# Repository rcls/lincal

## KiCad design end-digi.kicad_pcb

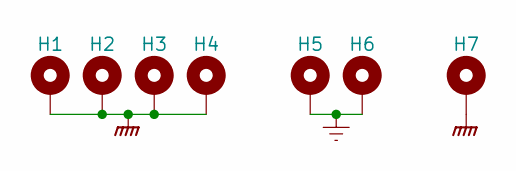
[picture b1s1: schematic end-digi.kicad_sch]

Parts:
H1, H2, H3, H4: MountingHole_Pad; MountingHole_3.2mm_M3_DIN965_Pad
H5, H6, H7: MountingHole_Pad; MountingHole_6.8mm

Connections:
Earth: H5.1, H6.1
GNDPWR: H1.1, H2.1, H3.1, H4.1, H7.1

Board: 2 copper layers, 7 parts (0 on the bottom side), 2 nets, no tracks yet.

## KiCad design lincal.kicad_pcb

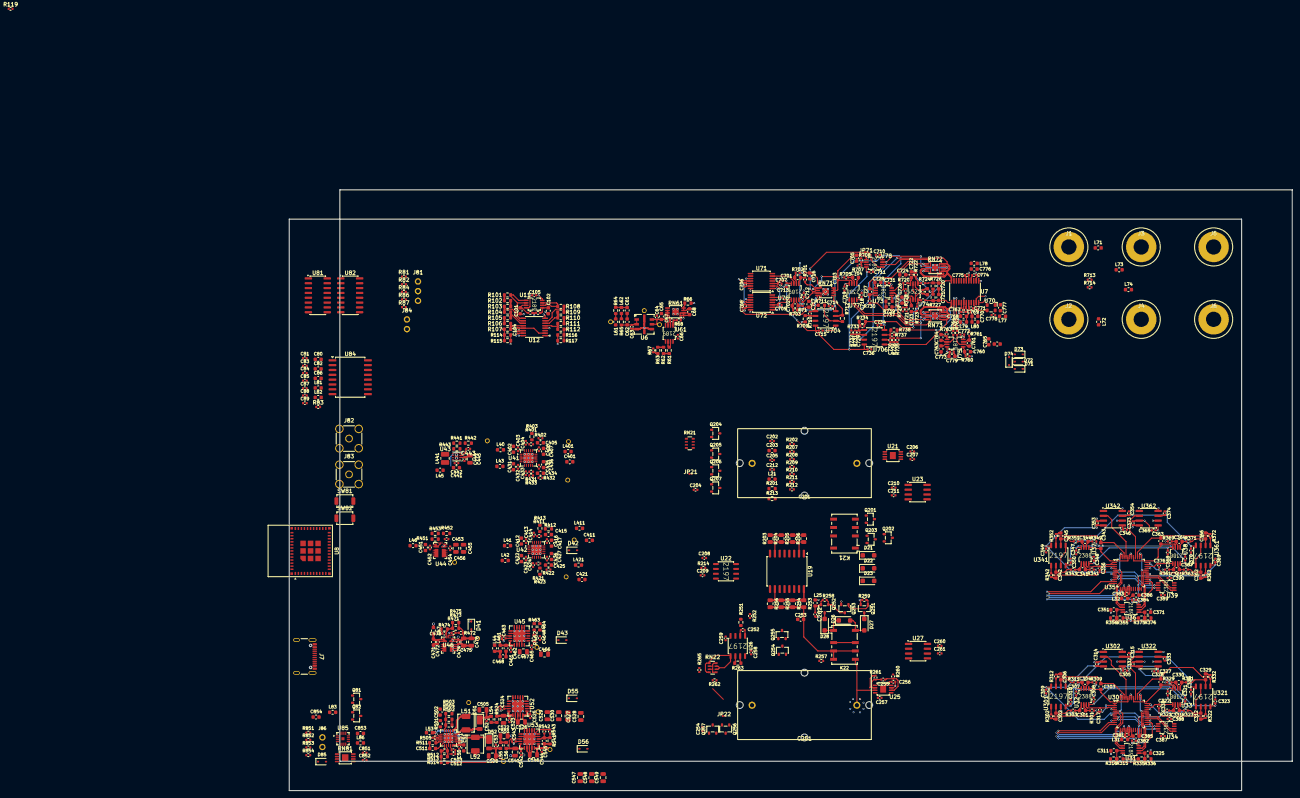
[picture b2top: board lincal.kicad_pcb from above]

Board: 4 copper layers, 263.3 x 157.7 mm, 594 parts (0 on the bottom side), 325 nets.

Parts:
C50, C52, C53, C66, C85, C87, C88, C89, C105, C206, C207, C208, C209, C210, C211, C256, C257, C258, C259, C260, C261, C309, C310, C314, C315, C323, C324, C332, C333, C349, C350, C353, C354, C369, C370, C373, C374, C382, C384, C523, C525, C542, C544, C706, C707, C708, C709, C710, C711, C712, C713, C714, C715, C734, C736, C772, C773: 0u1; C_0402_1005Metric
C51, C61, C62, C65, C80, C82, C86, C385, C386, C401, C402, C407, C411, C412, C417, C421, C422, C427, C431, C436, C441, C451, C461, C468, C471, C725, C733, C768, C770, C776, C777, C779, C853, C854: 10u; C_0603_1608Metric
C63, C64, C81, C83, C84, C104, C212, C262, C305, C307, C308, C321, C322, C327, C346, C347, C348, C365, C367, C368, C381, C383, C387, C388, C389, C390, C403, C404, C406, C413, C414, C416, C423, C424, C426, C432, C433, C435, C442, C444, C452, C454, C462, C463, C465, C472, C474, C503, C512, C524, C543, C718, C719, C731, C732, C767, C769, C771, C774, C775, C778, C851, C852: 1u; C_0402_1005Metric
C67, C202, C204, C205, C252, C254, C255, C317, C335, C356, C376, C703: 0n1; C_0402_1005Metric
C68, C101, C102, C203, C253, C311, C325, C351, C371, C405, C415, C425, C434, C464, C545, C716, C717, C720, C721, C727, C728, C760, C762, C763, C765: 10n; C_0603_1608Metric
C201, C251: 10u; C_Rect_L31.5mm_W15.0mm_P27.50mm_MKS4
C301, C302, C303, C304, C306, C312, C328, C329, C330, C331, C341, C342, C343, C344, C345, C361, C362, C363, C364, C366, C511, C701, C702, C704, C705, C722, C723, C724, C761, C764: 330p; C_0603_1608Metric
C443: 220p; C_0402_1005Metric
C445, C455, C456, C466, C467, C475, C476: 22u; C_0805_2012Metric
C453, C473: 22p; C_0402_1005Metric
C502: 1n; C_0603_1608Metric
C505, C508, C522, C526, C527, C528, C529, C530, C541, C546, C547, C548, C549, C551: 10u; C_0805_2012Metric
C726: 470n; C_0402_1005Metric
C729, C730: 10p; C_0402_1005Metric
C737: 10p; C_0603_1608Metric
D21, D22, D23, D26, D27, D28: SM4007PL; D_SOD-123FL
D41, D42, D43, D55, D56, D71, D72, D73, D74: 1N5819WS; D_SOD-323
D51, D52: DFLS140; D_PowerDI-123
D85: BZX384 5V6; D_SOD-323
J1, J2, J3, J4, J5, J6: Conn_01x01_Socket; Plated_Hole_D4.0mm_10mm
J7: USB_C_Receptacle_USB2.0_16P; USB_C_Receptacle_GCT_USB4105-xx-A_16P_TopMnt_Horizontal
J81: Conn_01x03_Pin; PinHeader_1x03_P2.54mm_Vertical
J82, J83: Conn_Coaxial; SMA_Amphenol_901-144_Vertical
J84, J86: Conn_01x02_Pin; PinHeader_1x02_P2.54mm_Vertical
JP21, JP22: SolderJumper_2_Open; JumperOpen
JP71: SolderJumper_2_Bridged; JumperClosed
K21, K22: G6K-2FY, 5V; Relay_DPDT_Omron_G6K-2G-Y
L21, L25, L31, L32, L40, L41, L42, L43, L44, L45, L47, L54, L55, L56, L61, L62, L77, L78, L79, L80, L82, L83, L401, L411, L421, L461: 600; L_0603_1608Metric
L46, L53, L71, L72, L73, L74, L81, L86: 100; L_0603_1608Metric
L51, L52: 10u; L_TechFuse_SL0420
L441: 1u5; L_1008_2520Metric
NT61: NetTie_2; NetTie-2_SMD_Pad0.5mm
Q81: Si2301CDS; SOT-23
Q82, Q201, Q203, Q204, Q205, Q206, Q207, Q251, Q253, Q254, Q255, Q256, Q257: AO3400A; SOT-23
Q202, Q252: AO3401A; SOT-23
R61, R62, R726, R727: 10k; R_0603_1608Metric
R63, R524: 1; R_0603_1608Metric
R64, R65: 2R2; R_0603_1608Metric
R66: 4k99; R_0603_1608Metric
R67, R81, R86, R87, R207, R208, R257, R258, R401, R411, R421, R431, R472, R542, R728, R729, R731, R736: 10k; R_0402_1005Metric
R68, R71, R210, R260, R701, R714, R724, R725, R761, R763: 10; R_0402_1005Metric
R82, R212, R262, R720, R721, R722, R723: 1k; R_0402_1005Metric
R83: 33; R_0402_1005Metric
R84, R113, R118, R119, R713, R730, R760: 100; R_0402_1005Metric
R101, R102, R103, R104, R109: 604; R_0603_1608Metric
R105, R106, R107, R110, R111, R112, R315, R316, R335, R336, R355, R356, R375, R376: 100; R_0603_1608Metric
R108: 47k5; R_0603_1608Metric
R114: 1k37; R_0603_1608Metric
R115: 150k; R_0603_1608Metric
R116: 24k9; R_0603_1608Metric
R117: 1M5; R_0603_1608Metric
R201, R251, R709: 16k; R_0603_1608Metric
R202, R209, R252, R259, R543, R710, R732, R735, R853, R854: 100k; R_0402_1005Metric
R203, R204, R205, R206, R253, R254, R255, R256: 1k; R_0805_2012Metric
R211, R261, R301, R302, R303, R309, R311, R312, R321, R322, R323, R329, R331, R332, R341, R342, R343, R349, R351, R352, R361, R362, R363, R369, R371, R372, R702, R703, R705, R707, R708, R762, R764: 330; R_0402_1005Metric
R213, R263: 8k2; R_0603_1608Metric
R214, R265: 200; R_0402_1005Metric
R402, R432, R505: 51k; R_0402_1005Metric
R403: 180k; R_0603_1608Metric
R412, R451, R473: 30k; R_0603_1608Metric
R413: 240k; R_0603_1608Metric
R422, R462: 20k; R_0402_1005Metric
R423: 160k; R_0603_1608Metric
R433: 56k; R_0402_1005Metric
R441: 2M; R_0603_1608Metric
R442: 360k; R_0603_1608Metric
R443: 91k; R_0603_1608Metric
R452, R474, R541: 130k; R_0603_1608Metric
R453, R475: 750k; R_0603_1608Metric
R463: 24k; R_0603_1608Metric
R464: 68k; R_0603_1608Metric
R471: 22k; R_0402_1005Metric
R501, R711, R712: 33k; R_0603_1608Metric
R502: 43k; R_0603_1608Metric
R503, R514: 1M; R_0603_1608Metric
R504: 1M3; R_0603_1608Metric
R511: 75k; R_0603_1608Metric
R512: 39k; R_0603_1608Metric
R513: 2M7; R_0603_1608Metric
R733, R737: 1k5; R_0402_1005Metric
R734, R738: 12k; R_0603_1608Metric
R739: 2k4; R_0603_1608Metric
R851, R852: 5k1; R_0402_1005Metric
RN21, RN22: 100R × 4; R_Array_Convex_4x0603
RN61, RN71, RN72, RN73, RN81: LT5400-1; MSOP-8-1EP_3x3mm_P0.65mm_EP1.68x1.88mm
SW81, SW82: SW_Push; SW_SPST_TS-1088-xR020
TP41, TP42, TP43, TP44, TP45, TP46, TP47, TP48, TP51, TP52, TP53, TP54, TP61, TP62, TP63: TestPoint
U6: REF7050; FKH0008A-MFG
U7: AD7177-2BRUZ; TSSOP-24_4.4x7.8mm_P0.65mm
U8: ESP32-C6-MINI-1U; ESP32-C6-MINI-1
U11, U31, U36, U61, U75, U76, U78: OPA2189DGK; OPA2189
U12: TMUX1108PW; TSSOP-16_4.4x5mm_P0.65mm
U19: TCA0372; SOIC-16W_7.5x10.3mm_P1.27mm
U21, U25: OPA828DGN; VSSOP-8-1EP_3x3mm_P0.65mm_EP1.57x1.89mm
U22, U26, U301, U321, U341, U361, U704, U706: OPA2197D; OPA2197
U23, U27, U302, U322, U342, U362: DG419D; SOIC-8_3.9x4.9mm_P1.27mm
U30, U35: LTC2752B; LQFP-48_7x7mm_P0.5mm
U32, U33, U34, U37, U38, U39, U73, U77: OPA2388DGK; OPA2388
U41, U42: TPS7A8801RTJR; QFN-20-1EP_4x4mm_P0.5mm_EP2.7x2.7mm
U43: TPS61252DSG; WSON-8-1EP_2x2mm_P0.5mm_EP0.9x1.6mm
U44, U46: TPSM863252RDXR; RDX0007A-MFG
U45, U53: TPS7A3301RGW; Texas_RGW0020A_VQFN-20-1EP_5x5mm_P0.65mm_EP3.15x3.15mm
U51: ADP5071ACPZ; LFCSP-20-1EP_4x4mm_P0.5mm_EP2.6x2.6mm
U52: TPS7A4700xRGW; Texas_RGW0020A_VQFN-20-1EP_5x5mm_P0.65mm_EP3.15x3.15mm
U70: TG2520SMN-16M-MCG; TG2520SMN
U71, U72: TMUX6104; TSSOP-14_4.4x5mm_P0.65mm
U74: THS4521IDGK; OPA4521
U81, U82: 74HC595; SOIC-16_3.9x9.9mm_P1.27mm
U84: ISOW7842; SOIC-16W_7.5x10.3mm_P1.27mm
U85: DAC80508xRTE; Texas_RTE0016D_WQFN-16-1EP_3x3mm_P0.5mm_EP0.8x0.8mm

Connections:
+2V5: C307.1, C321.1, C347.1, C367.1, C387.1, C389.1, C425.1, C426.1, C427.1, C718.1, D42.1 (K), L80.1, R422.1, TP45.1, U32.8 (V+), U33.8 (V+), U34.8 (V+), U37.8 (V+), U38.8 (V+), U39.8 (V+), U42.11 (OUT2), U42.12 (OUT2), U71.2 (EN), U72.2 (EN), U77.8 (V+)
+3V3: C453.1, C454.1, C455.1, C456.1, C852.1, L42.1, L81.1, L82.1, R81.2, R86.1, R452.1, TP43.1, U44.3 (VOUT), U85.16 (VIO)
+3V3A: C88.1, C89.1, C305.1, C327.1, C346.1, C365.1, C415.1, C416.1, C417.1, L31.1, L32.1, L77.1, L78.1, R87.2, R412.1, TP44.1, U23.5 (V_{L}), U27.5 (V_{L}), U42.14 (OUT1), U42.15 (OUT1), U81.16 (VCC), U82.16 (VCC), U302.5 (V_{L}), U322.5 (V_{L}), U342.5 (V_{L}), U362.5 (V_{L})
+5V: C853.1, J86.2, L41.1, L45.1, L47.1, L53.1, Q81.3 (D)
+5V6A: C434.1, C435.1, C436.1, L61.1, R432.1, TP47.1, U41.11 (OUT2), U41.12 (OUT2)
+5VA: C104.1, C405.1, C406.1, C407.1, C731.1, C732.1, C733.1, D71.1 (K), L79.1, L83.1, R402.1, R728.2, TP41.1, U12.2 (EN), U12.13 (VDD), U41.14 (OUT1), U41.15 (OUT1), U73.4 (V-), U74.3 (V_{S+}), U74.7 (~PD)
+5VP: D85.1 (K), J86.1, L46.1, L86.2, Q81.2 (S), R853.1
+6V: C443.1, C444.1, C445.1, L21.1, L25.1, L40.1, L43.1, R442.1, TP42.1, U43.2 (VOUT)
+18V: C66.1, C105.1, C206.1, C208.1, C210.1, C256.1, C258.1, C260.1, C309.1, C314.1, C323.1, C332.1, C349.1, C353.1, C369.1, C373.1, C382.1, C384.1, C525.2, C526.2, C527.2, C528.2, C529.2, C530.2, C706.1, C708.1, C710.1, C712.1, C714.1, C734.1, C772.1, D55.1 (K), TP52.1, U11.8 (V+), U21.7 (V+), U22.8 (V+), U23.4 (VDD), U25.7 (V+), U26.8 (V+), U27.4 (VDD), U31.8 (V+), U36.8 (V+), U52.1 (OUT), U52.3 (SENSE/FB), U52.20 (OUT), U61.8 (V+), U71.12 (VDD), U72.12 (VDD), U75.8 (V+), U76.8 (V+), U78.8 (V+), U301.8 (V+), U302.4 (VDD), U321.8 (V+), U322.4 (VDD), U341.8 (V+), U342.4 (VDD), U361.8 (V+), U362.4 (VDD), U704.8 (V+), U706.8 (V+)
-2V5: C308.2, C322.2, C348.2, C368.2, C388.2, C390.2, C464.1, C465.2, C466.1, C467.1, C719.2, C773.2, C779.2, D43.2 (A), R66.2, R67.2, R114.2, R115.1, R116.2, R117.1, R462.1, TP46.1, U32.4 (V-), U33.4 (V-), U34.4 (V-), U37.4 (V-), U38.4 (V-), U39.4 (V-), U45.1 (OUT), U45.20 (OUT), U75.4 (V-), U77.4 (V-)
-3V3: C471.2, C472.2, C474.2, C475.2, C476.2, D41.2 (A), L44.1, R472.2, R473.2, R475.2, TP48.1, U46.4 (PGND)
-18V: C207.2, C209.2, C211.2, C257.2, C259.2, C261.2, C310.2, C315.2, C324.2, C333.2, C350.2, C354.2, C370.2, C374.2, C544.1, C545.1, C546.1, C547.1, C548.1, C549.1, C707.2, C709.2, C711.2, C713.2, C715.2, C736.2, D56.2 (A), R541.1, TP54.1, U21.4 (V-), U22.4 (V-), U23.7 (VSS), U25.4 (V-), U26.4 (V-), U27.7 (VSS), U53.1 (OUT), U53.20 (OUT), U71.3 (VSS), U72.3 (VSS), U76.4 (V-), U78.4 (V-), U301.4 (V-), U302.7 (VSS), U321.4 (V-), U322.7 (VSS), U341.4 (V-), U342.7 (VSS), U361.4 (V-), U362.7 (VSS), U704.4 (V-), U706.4 (V-)
/18V/P5V: C50.2, C51.1, L53.2, U51.7 (EN1), U51.9 (EN2), U51.15 (PVIN1), U51.16 (PVINSYS), U51.17 (PVIN2)
/18V/VRef: C512.1, R512.1, R513.1, U51.12 (VREF)
/18V/i18: C522.1, C523.1, R524.1, U52.13 (EN), U52.15 (IN), U52.16 (IN)
/18V/im18: C541.1, C542.1, L56.2, U53.13 (EN), U53.15 (IN), U53.16 (IN)
/ADC+: C721.2, R725.1, R727.2, R737.2, R738.2, RN73.1, RN73.4, RN73.6, U7.1 (AIN4), U706.5 (+)
/ADC-: C720.1, R724.1, R726.1, R733.2, R734.2, RN72.1, RN72.4, RN72.7, U7.24 (AIN3), U706.3 (+)
/CPU/LATCH: U8.28 (IO22), U81.12 (RCLK), U82.12 (RCLK)
/CPU/TRIGIN: U8.10 (IO5), U84.4 (INB)
/CPU/TRIGOUT: U8.6 (IO3), U84.5 (OUTC)
/CPU/~SRCLR: C87.1, R87.1, U81.10 (~SRCLR), U82.10 (~SRCLR)
/DAC1A: U71.5 (S2), U302.1 (D)
/DAC1B: U72.5 (S2), U322.1 (D)
/DAC2A: U71.11 (S3), U342.1 (D)
/DAC2B: U72.11 (S3), U362.1 (D)
/DAC2752-1A/FREF: C317.2, R302.1, U30.1 (REFA), U30.2 (REFA), U301.1
/DAC2752-1A/Force: C303.2, R312.1, U30.46 (RFBA), U301.7
/DAC2752-1A/IOUT1: C303.1, U30.44 (IOUT1A), U32.5 (+)
/DAC2752-1A/RCOM: C317.1, U30.3 (RCOMA), U32.3 (+)
/DAC2752-1A/RIN: U30.5 (RINA), U30.47 (ROFSA), U30.48 (ROFSA), U31.1
/DAC2752-1A/RSense: U30.6 (RINA), U31.2 (-)
/DAC2752-1A/Sense: U30.45 (RFBA), U302.2 (S1)
/DAC2752-1B/FREF: C335.2, R322.1, U30.35 (REFB), U30.36 (REFB), U321.7
/DAC2752-1B/Force: C328.2, R332.1, U30.39 (RFBB), U321.1
/DAC2752-1B/IOUT1: C328.1, U30.41 (IOUT1B), U33.3 (+)
/DAC2752-1B/RCOM: C335.1, U30.34 (RCOMB), U33.5 (+)
/DAC2752-1B/RIN: U30.32 (RINB), U30.37 (ROFSB), U30.38 (ROFSB), U31.7
/DAC2752-1B/RSense: U30.31 (RINB), U31.6 (-)
/DAC2752-1B/Sense: U30.40 (RFBB), U322.2 (S1)
/DAC2752-2A/FREF: C356.2, R342.1, U35.1 (REFA), U35.2 (REFA), U341.1
/DAC2752-2A/Force: C343.2, R352.1, U35.46 (RFBA), U341.7
/DAC2752-2A/IOUT1: C343.1, U35.44 (IOUT1A), U37.5 (+)
/DAC2752-2A/RCOM: C356.1, U35.3 (RCOMA), U37.3 (+)
/DAC2752-2A/RIN: U35.5 (RINA), U35.47 (ROFSA), U35.48 (ROFSA), U36.1
/DAC2752-2A/RSense: U35.6 (RINA), U36.2 (-)
/DAC2752-2A/Sense: U35.45 (RFBA), U342.2 (S1)
/DAC2752-2B/FREF: C376.2, R362.1, U35.35 (REFB), U35.36 (REFB), U361.7
/DAC2752-2B/Force: C363.2, R372.1, U35.39 (RFBB), U361.1
/DAC2752-2B/IOUT1: C363.1, U35.41 (IOUT1B), U38.3 (+)
/DAC2752-2B/RCOM: C376.1, U35.34 (RCOMB), U38.5 (+)
/DAC2752-2B/RIN: U35.32 (RINB), U35.37 (ROFSB), U35.38 (ROFSB), U36.7
/DAC2752-2B/RSense: U35.31 (RINB), U36.6 (-)
/DAC2752-2B/Sense: U35.40 (RFBB), U362.2 (S1)
/FDA/Force+: R723.1, R725.2, U74.4
/FDA/Force-: C724.2, R722.1, R724.2, U74.5
/FDA/ForceCM: C726.1, R730.1, U74.2 (V_{OCM})
/FDA/In+Fb-: C724.1, RN72.2, RN72.3, RN72.5, RN72.8, U73.3 (+)
/FDA/In-Fb+: C737.2, RN73.2, RN73.3, RN73.5, RN73.8, U73.2 (-)
/FDA/S2Bias: C725.1, R721.2, R728.1, R729.1
/FDA/SenseCM: C727.2, R726.2, R727.1, U73.6 (-)
/FDA/Stage1: R720.2, R739.1, U73.1
/LTC2752 Common/3V3-1: C381.1, C385.1, L31.2, U30.16 (VDD), U30.19 (~CLR)
/LTC2752 Common/3V3-2: C383.1, C386.1, L32.2, U35.16 (VDD), U35.19 (~CLR)
/Low Voltage Power/I2V5: C422.1, C423.1, L421.2, U42.4 (IN2), U42.5 (IN2), U42.6 (EN2)
/Low Voltage Power/I3V3: C451.1, C452.1, L46.2, U44.1 (VIN), U44.6 (EN)
/Low Voltage Power/I3V3A: C412.1, C413.1, L411.2, U42.1 (IN1), U42.2 (IN1), U42.20 (EN1)
/Low Voltage Power/I5V6A: C431.1, C432.1, L43.2, U41.4 (IN2), U41.5 (IN2), U41.6 (EN2)
/Low Voltage Power/I5VA: C402.1, C403.1, L401.2, U41.1 (IN1), U41.2 (IN1), U41.20 (EN1)
/Low Voltage Power/I6V: C441.1, C442.1, L45.2, L441.1, U43.4 (ILIM), U43.6 (EN), U43.8 (VIN)
/Low Voltage Power/Im2V5: C461.1, C462.1, L461.2, U45.13 (EN), U45.15 (IN), U45.16 (IN)
/Low Voltage Power/Im3V3: C471.1, C472.1, L47.2, R471.1, U46.1 (VIN)
/MISO: U7.11 (DOUT/~RDY), U8.5 (IO2), U30.14 (SRO), U35.14 (SRO), U85.15 (SDO)
/MOSI: U7.12 (DIN), U8.16 (IO7), U30.12 (SDI), U35.12 (SDI), U81.14 (SER), U85.14 (SDI)
/MonA0: U71.1 (A0), U82.3 (QD)
/MonA1: U71.14 (A1), U82.2 (QC)
/MonB0: U72.1 (A0), U82.1 (QB)
/MonB1: U72.14 (A1), U82.15 (QA)
/MonTC: R709.2, U85.2 (OUT0)
/Monitor ADC/16M: U7.10 (XTAL2/CLKIO), U70.3 (OUT)
/Monitor ADC/BufR+: C762.1, D71.2 (A), D72.1 (K), R761.2, R762.2, U7.3 (REF+)
/Monitor ADC/BufR-: C765.1, D73.2 (A), D74.1 (K), R763.2, R764.2, U7.2 (REF-)
/Monitor/AddendA: L71.2, U71.6 (D), U76.3 (+)
/Monitor/AddendB: L72.2, U72.6 (D), U76.5 (+)
/Monitor/BufA: C716.2, L73.1, R701.2, R702.2, RN71.1
/Monitor/BufB: C717.2, L74.1, R71.2, R703.2, RN71.3
/Monitor/FbA: C701.2, R702.1, U76.2 (-)
/Monitor/FbB: C702.1, R703.1, U76.6 (-)
/Monitor/Isum: C703.1, C705.2, JP71.1 (A), RN71.2, U78.1
/Monitor/TC+: R712.1, RN71.5, U704.7
/Monitor/TC-: R710.1, R711.2, RN71.4, U704.1
/Monitor/Vg: C703.2, RN71.6, RN71.7, RN71.8, U77.3 (+)
/Offset: U12.8 (D), U72.10 (S4)
/Offset Voltage Ladder/0V01: R111.1, R112.1, U12.5 (S2)
/Offset Voltage Ladder/0V03: R109.2, R110.1, U12.6 (S3)
/Offset Voltage Ladder/0V09: R108.2, R109.1, U12.7 (S4)
/Offset Voltage Ladder/0V18: R106.1, R107.1, U12.12 (S5)
/Offset Voltage Ladder/0V55: R104.2, R105.1, U12.11 (S6)
/Offset Voltage Ladder/1V66: R103.1, R104.1, U12.10 (S7)
/Offset Voltage Ladder/5V: R119.2, U12.9 (S8)
/Offset Voltage Ladder/L5V: R108.1, U11.6 (-), U11.7
/OffsetA0: U12.1 (A0), U81.7 (QH)
/OffsetA1: U12.16 (A1), U81.6 (QG)
/OffsetA2: U12.15 (A2), U81.5 (QF)
/Ref2V16: U85.3 (OUT1), U704.3 (+)
/Reference/rin: C62.1, C63.1, R65.1, TP61.1, U6.1 (EN), U6.2 (VIN)
/SCK: U7.13 (SCLK), U8.15 (IO6), U30.13 (SCK), U35.13 (SCK), U81.11 (SRCLK), U82.11 (SRCLK), U85.13 (SCLK)
/Sample Hold 1/Drive: C203.2, K21.3, K21.4, K21.6, R203.2, R204.2, R205.2, R206.2
/Sample Hold 1/HoldGnd: Q206.1 (G), Q207.1 (G)
/Sample Hold 1/SH: C201.1, K21.5, U21.3 (+)
/Sample Hold 1/SHGnd: C201.2, JP21.1 (A), Q204.2 (S), R212.1, RN21.2 (R2.1), RN21.3 (R3.1), RN21.5 (R4.2), RN21.8 (R1.2)
/Sample Hold 1/Sample: Q201.1 (G), Q203.1 (G), R209.1
/Sample Hold 1/SampleGnd: Q204.1 (G), Q205.1 (G)
/Sample Hold 2/Drive: C253.2, K22.3, K22.4, K22.6, R253.2, R254.2, R255.2, R256.2
/Sample Hold 2/HoldGnd: Q256.1 (G), Q257.1 (G)
/Sample Hold 2/SH: C251.1, K22.5, U25.3 (+)
/Sample Hold 2/SHGnd: C251.2, JP22.1 (A), Q254.2 (S), R262.1, RN22.2 (R2.1), RN22.3 (R3.1), RN22.5 (R4.2), RN22.8 (R1.2)
/Sample Hold 2/Sample: Q251.1 (G), Q253.1 (G), R259.1
/Sample Hold 2/SampleGnd: Q254.1 (G), Q255.1 (G)
/Sel1A: U82.7 (QH), U302.6 (SEL)
/Sel1B: U82.6 (QG), U322.6 (SEL)
/Sel2A: U82.5 (QF), U342.6 (SEL)
/Sel2B: U82.4 (QE), U362.6 (SEL)
/Sum+: R732.2, RN72.6, U78.6 (-), U78.7
/Sum-: R735.2, RN73.7, U77.6 (-), U77.7
/~CSAUX: U8.26 (IO20), U85.12 (~CS)
/~CSDAC1: U8.24 (IO18), U30.11 (~CS/LD)
/~CSDAC2: U8.25 (IO19), U35.11 (~CS/LD)
/~CSMON: U7.14 (~CS), U8.27 (IO21)
/~LDAC: U8.29 (IO23), U30.26 (~LDAC), U35.26 (~LDAC)
Earth: J82.2 (Ext), J83.2 (Ext), U84.9 (GND2), U84.10 (SEL), U84.11 (IND), U84.15 (GND2)
GND: C64.2, C65.2, C68.2, C101.2, C102.2, C204.2, C254.2, C311.2, C325.2, C351.2, C371.2, C760.2, C762.2, C763.2, C765.2, NT61.2, Q207.2 (S), Q257.2 (S), R63.2, R66.1, R67.1, R107.2, R112.2, R114.1, R115.2, R116.1, R117.2, R214.2, R265.2, R301.2, R309.1, R321.2, R329.1, R341.2, R349.1, R361.2, R369.1, R705.2, R714.1, RN21.1 (R1.1), RN21.4 (R4.1), RN21.6 (R3.2), RN21.7 (R2.2), RN22.1 (R1.1), RN22.4 (R4.1), RN22.6 (R3.2), RN22.7 (R2.2), RN61.3, RN61.4, RN61.9, TP63.1, U6.8 (GND), U12.4 (S1), U22.5 (+), U26.5 (+), U30.4 (GEADJA), U30.33 (GEADJB), U30.42 (VOSADJB), U30.43 (VOSADJA), U34.3 (+), U34.5 (+), U35.4 (GEADJA), U35.33 (GEADJB), U35.42 (VOSADJB), U35.43 (VOSADJA), U39.3 (+), U39.5 (+), U77.5 (+), U78.3 (+), U301.3 (+), U301.5 (+), U302.8 (S2), U321.3 (+), U321.5 (+), U322.8 (S2), U341.3 (+), U341.5 (+), U342.8 (S2), U361.3 (+), U361.5 (+), U362.8 (S2)
GNDPWR: C50.1, C51.2, C52.2, C53.1, C61.2, C62.2, C63.2, C66.2, C80.2, C81.2, C82.2, C83.2, C84.2, C85.2, C86.2, C87.2, C88.2, C89.2, C104.2, C105.2, C203.1, C206.2, C207.1, C208.2, C209.1, C210.2, C211.1, C212.2, C253.1, C256.2, C257.1, C258.2, C259.1, C260.2, C261.1, C262.2, C305.2, C307.2, C308.1, C309.2, C310.1, C314.2, C315.1, C321.2, C322.1, C323.2, C324.1, C327.2, C332.2, C333.1, C346.2, C347.2, C348.1, C349.2, C350.1, C353.2, C354.1, C365.2, C367.2, C368.1, C369.2, C370.1, C373.2, C374.1, C381.2, C382.2, C383.2, C384.2, C385.2, C386.2, C387.2, C388.1, C389.2, C390.1, C401.2, C402.2, C403.2, C404.2, C406.2, C407.2, C411.2, C412.2, C413.2, C414.2, C416.2, C417.2, C421.2, C422.2, C423.2, C424.2, C426.2, C427.2, C431.2, C432.2, C433.2, C435.2, C436.2, C441.2, C442.2, C444.2, C445.2, C451.2, C452.2, C454.2, C455.2, C456.2, C461.2, C462.2, C463.1, C465.1, C466.2, C467.2, C468.2, C473.1, C474.1, C475.1, C476.1, C502.1, C503.1, C505.2, C508.1, C511.1, C512.2, C522.2, C523.2, C524.1, C525.1, C526.1, C527.1, C528.1, C529.1, C530.1, C541.2, C542.2, C543.2, C544.2, C546.2, C547.2, C548.2, C549.2, C551.2, C706.2, C707.1, C708.2, C709.1, C710.2, C711.1, C712.2, C713.1, C714.2, C715.1, C716.1, C717.1, C718.2, C719.1, C720.2, C721.1, C725.2, C726.2, C728.2, C731.2, C732.2, C733.2, C734.2, C736.1, C767.2, C768.2, C769.2, C770.2, C771.2, C772.2, C773.1, C774.2, C775.2, C776.2, C777.2, C778.2, C779.1, C851.2, C852.2, C853.2, C854.2, D41.1 (K), D42.2 (A), D43.1 (K), D55.2 (A), D56.1 (K), D72.2 (A), D73.1 (K), D74.2 (A), D85.2 (A), J7.A1 (GND), J7.A12 (GND), J7.B1 (GND), J7.B12 (GND), J7.S1 (SHIELD), J81.3, J84.2, L52.2, NT61.1, Q82.2 (S), Q201.2 (S), Q203.2 (S), Q205.2 (S), Q251.2 (S), Q253.2 (S), Q255.2 (S), R209.2, R259.2, R401.2, R403.2, R411.2, R413.2, R421.2, R423.2, R431.2, R433.2, R441.2, R443.2, R451.2, R453.2, R463.2, R464.2, R474.1, R502.2, R504.2, R505.2, R542.2, R543.2, R729.2, R851.2, R852.2, R854.1, RN71.9, RN72.9, RN73.9, RN81.1, RN81.2, RN81.3, RN81.4, RN81.5, RN81.6, RN81.7, RN81.8, RN81.9, SW81.2, SW82.2, U6.3 (GND), U6.4 (GND), U6.5 (GND), U7.6 (AVSS), U7.17 (DGND), U8.1 (GND), U8.2 (GND), U8.11 (GND), U8.14 (GND), U8.36 (GND), U8.37 (GND), U8.38 (GND), U8.39 (GND), U8.40 (GND), U8.41 (GND), U8.42 (GND), U8.43 (GND), U8.44 (GND), U8.45 (GND), U8.46 (GND), U8.47 (GND), U8.48 (GND), U8.49 (GND), U8.50 (GND), U8.51 (GND), U8.52 (GND), U8.53 (GND), U11.4 (V-), U12.3 (VSS), U12.14 (GND), U21.9, U23.3 (GND), U25.9, U27.3 (GND), U30.7 (GND), U30.10 (GND), U30.15 (GND), U30.17 (GND), U30.18 (GND), U30.22 (M-SPAN), U30.23 (S0), U30.24 (S1), U30.25 (S2), U30.27 (GND), U30.30 (GND), U31.4 (V-), U35.7 (GND), U35.10 (GND), U35.15 (GND), U35.17 (GND), U35.18 (GND), U35.22 (M-SPAN), U35.23 (S0), U35.24 (S1), U35.25 (S2), U35.27 (GND), U35.30 (GND), U36.4 (V-), U41.3 (GND), U41.8 (SS_CTRL2), U41.13 (GND), U41.18 (SS_CTRL1), U41.21 (GND), U42.3 (GND), U42.8 (SS_CTRL2), U42.13 (GND), U42.18 (SS_CTRL1), U42.21 (GND), U43.1 (GND), U43.9 (GND), U44.4 (PGND), U45.2 (NC), U45.4 (NC), U45.5 (NC), U45.6 (NC), U45.7 (GND), U45.8 (NC), U45.9 (NC), U45.10 (NC), U45.11 (NC), U45.12 (NC), U45.17 (NC), U45.18 (NC), U45.19 (NC), U45.21 (EP), U46.3 (VOUT), U51.2 (SYNC/FREQ), U51.13 (AGND), U51.19 (PGND), U51.21 (AGND), U52.4 (6.4V), U52.5 (6.4V), U52.6 (3.2V), U52.7 (GND), U52.10 (0.4V), U52.11 (0.2V), U52.17 (NC), U52.18 (NC), U52.19 (NC), U52.21 (EP), U53.2 (NC), U53.4 (NC), U53.5 (NC), U53.6 (NC), U53.7 (GND), U53.8 (NC), U53.9 (NC), U53.10 (NC), U53.11 (NC), U53.12 (NC), U53.17 (NC), U53.18 (NC), U53.19 (NC), U53.21 (EP), U61.4 (V-), U70.2 (GND), U71.13 (GND), U72.13 (GND), U73.8 (V+), U74.6 (V_{S-}), U81.8 (GND), U81.13 (~OE), U82.8 (GND), U82.13 (~OE), U84.2 (GND1), U84.3 (INA), U84.8 (GND1), U85.6 (GND), U85.17 (PAD), U302.3 (GND), U322.3 (GND), U342.3 (GND), U362.3 (GND), U704.5 (+)
unnamed: C61.1, L62.1, R64.1
unnamed: C67.1, R68.1, U61.1
unnamed: C205.1, R210.2, U21.6
unnamed: C255.1, R260.2, U25.6
unnamed: C301.1, R303.2, U32.1
unnamed: C302.1, R302.2
unnamed: C304.1, R311.2, U32.7
unnamed: C306.1, R312.2
unnamed: C312.1, R322.2
unnamed: C329.1, R332.2
unnamed: C330.1, R331.2, U33.1
unnamed: C331.1, R323.2, U33.7
unnamed: C341.1, R343.2, U37.1
unnamed: C342.1, R342.2
unnamed: C344.1, R351.2, U37.7
unnamed: C345.1, R352.2
unnamed: C361.1, R363.2, U38.7
unnamed: C362.1, R362.2
unnamed: C364.1, R371.2, U38.1
unnamed: C366.1, R372.2
unnamed: C401.1, L40.2, L401.1
unnamed: C411.1, L41.2, L411.1
unnamed: C421.1, L42.2, L421.1
unnamed: C468.1, L44.2, L461.1
unnamed: C502.2, R501.2
unnamed: C511.2, R511.2
unnamed: C551.1, L55.2, L56.1
unnamed: C701.1, R701.1, U76.1
unnamed: C702.2, R71.1, U76.7
unnamed: C704.1, R707.2, U77.1
unnamed: C705.1, R708.1
unnamed: C722.2, R722.2
unnamed: C723.1, R723.2
unnamed: C727.1, R730.2, U73.7
unnamed: C729.1, R731.1, R733.1, R734.1, U706.1
unnamed: C730.2, R736.2, R737.1, R738.1, U706.7
unnamed: C737.1, R739.2
unnamed: C761.1, R761.1, U75.7
unnamed: C764.1, R763.1, U75.1
unnamed: D21.2 (A), D22.2 (A), K21.8
unnamed: D21.1 (K), Q201.3 (D)
unnamed: D22.1 (K), D23.1 (K), K21.1, R207.1
unnamed: D23.2 (A), Q202.3 (D)
unnamed: D26.2 (A), D27.2 (A), K22.8
unnamed: D26.1 (K), D28.1 (K), K22.1, R257.1
unnamed: D27.1 (K), Q251.3 (D)
unnamed: D28.2 (A), Q252.3 (D)
unnamed: D51.2 (A), L51.2, U51.20 (SW1)
unnamed: C52.1, C505.1, D51.1 (K), L54.1, R503.1, TP51.1
unnamed: C53.2, C508.2, D52.2 (A), L55.1, R514.2, TP53.1
unnamed: D52.1 (K), L52.1, U51.18 (SW2)
unnamed: J1.1, L71.1
unnamed: J2.1, L72.1
unnamed: J3.1, L73.2
unnamed: J4.1, L74.2
unnamed: J5.1, R713.2
unnamed: J6.1, R714.2
unnamed: J7.A5 (CC1), R851.1
unnamed: J7.B5 (CC2), R852.1
unnamed: J7.A4 (VBUS), J7.A9 (VBUS), J7.B4 (VBUS), J7.B9 (VBUS), L86.1
unnamed: J81.1, U8.31 (TXD0)
unnamed: J81.2, U8.30 (RXD0)
unnamed: J82.1 (In), R83.2
unnamed: J83.1 (In), R84.2
unnamed: J84.1, SW82.1, U8.23 (IO9)
unnamed: C204.1, JP21.2 (B), Q206.2 (S)
unnamed: C254.1, JP22.2 (B), Q256.2 (S)
unnamed: JP71.2 (B), R713.1, U78.5 (+)
unnamed: K21.2, K21.7, R207.2
unnamed: K22.2, K22.7, R257.2
unnamed: L54.2, R524.2
unnamed: L61.2, R64.2
unnamed: L62.2, R65.2
unnamed: Q81.1 (G), Q82.3 (D), R853.2
unnamed: Q202.1 (G), Q203.3 (D), R208.2
unnamed: C212.1, L21.2, Q202.2 (S), R208.1
unnamed: Q204.3 (D), Q205.3 (D)
unnamed: Q206.3 (D), Q207.3 (D)
unnamed: Q252.1 (G), Q253.3 (D), R258.2
unnamed: C262.1, L25.2, Q252.2 (S), R258.1
unnamed: Q254.3 (D), Q255.3 (D)
unnamed: Q256.3 (D), Q257.3 (D)
unnamed: R81.1, R82.2, SW81.1
unnamed: R101.2, R102.2
unnamed: R102.1, R103.2
unnamed: R105.2, R106.2
unnamed: R110.2, R111.2
unnamed: R213.2, R214.1, U22.7
unnamed: R263.2, R265.1, U26.7
unnamed: C768.1, C769.1, L79.2, U7.7 (AVDD1)
unnamed: C770.1, C771.1, L80.2, U7.8 (AVDD2)
unnamed: C774.1, C776.1, L78.2, U7.16 (IOVDD)
unnamed: C767.1, U7.5 (REGCAPA)
unnamed: C775.1, U7.18 (REGCAPD)
unnamed: C80.1, C81.1, L81.2, U8.3 (3V3)
unnamed: C84.1, R82.1, U8.8 (EN)
unnamed: R86.2, U8.22 (IO8)
unnamed: C101.1, R113.2, U11.3 (+)
unnamed: R101.1, R119.1, U11.1, U11.2 (-)
unnamed: C102.1, R118.2, U11.5 (+)
unnamed: C252.2, U19.9 (+), U26.1
unnamed: R252.1, R253.1, R254.1, R255.1, R256.1, U19.10 (-), U19.16
unnamed: C202.2, U19.8 (+), U22.1
unnamed: R202.1, R203.1, R204.1, R205.1, R206.1, U19.2, U19.7 (-)
unnamed: C205.2, R211.2, U21.2 (-)
unnamed: C202.1, R201.1, R202.2, U22.2 (-)
unnamed: R212.2, R213.1, U22.6 (-)
unnamed: R210.1, R211.1, U23.2 (S1)
unnamed: C255.2, R261.2, U25.2 (-)
unnamed: C252.1, R251.1, R252.2, U26.2 (-)
unnamed: R262.2, R263.1, U26.6 (-)
unnamed: R260.1, R261.1, U27.2 (S1)
unnamed: U30.9 (IOUT2AF), U34.7
unnamed: U30.8 (IOUT2AS), U34.6 (-)
unnamed: U30.28 (IOUT2BF), U34.1
unnamed: U30.29 (IOUT2BS), U34.2 (-)
unnamed: C311.1, R315.1, R316.1, U31.3 (+)
unnamed: C325.1, R335.1, R336.1, U31.5 (+)
unnamed: C301.2, R301.1, U32.2 (-)
unnamed: C304.2, R309.2, U32.6 (-)
unnamed: C330.2, R329.2, U33.2 (-)
unnamed: C331.2, R321.1, U33.6 (-)
unnamed: U35.9 (IOUT2AF), U39.7
unnamed: U35.8 (IOUT2AS), U39.6 (-)
unnamed: U35.28 (IOUT2BF), U39.1
unnamed: U35.29 (IOUT2BS), U39.2 (-)
unnamed: C351.1, R355.1, R356.1, U36.3 (+)
unnamed: C371.1, R375.1, R376.1, U36.5 (+)
unnamed: C341.2, R341.1, U37.2 (-)
unnamed: C344.2, R349.2, U37.6 (-)
unnamed: C364.2, R369.2, U38.2 (-)
unnamed: C361.2, R361.1, U38.6 (-)
unnamed: C405.2, R401.1, R402.2, R403.1, U41.16 (FB1)
unnamed: C404.1, U41.19 (NR_SS1)
unnamed: C434.2, R431.1, R432.2, R433.1, U41.10 (FB2)
unnamed: C433.1, U41.7 (NR_SS2)
unnamed: C415.2, R411.1, R412.2, R413.1, U42.16 (FB1)
unnamed: C414.1, U42.19 (NR_SS1)
unnamed: C425.2, R421.1, R422.2, R423.1, U42.10 (FB2)
unnamed: C424.1, U42.7 (NR_SS2)
unnamed: C443.2, R441.1, R442.2, R443.1, U43.3 (FB)
unnamed: L441.2, U43.7 (SW)
unnamed: C453.2, R451.1, R452.2, R453.1, U44.7 (FB)
unnamed: C464.2, R462.2, R463.1, R464.1, U45.3 (FB)
unnamed: C463.2, U45.14 (NR/SS)
unnamed: R471.2, R472.1, U46.6 (EN)
unnamed: C473.2, R473.1, R474.2, R475.1, U46.7 (FB)
unnamed: R501.1, U51.6 (COMP1)
unnamed: R511.1, U51.10 (COMP2)
unnamed: R502.1, R503.2, R504.1, U51.5 (FB1)
unnamed: R512.2, R513.2, R514.1, U51.11 (FB2)
unnamed: L51.1, U51.1 (INBK)
unnamed: R505.1, U51.8 (SS)
unnamed: C503.2, U51.14 (VREG)
unnamed: C524.2, U52.14 (NR)
unnamed: C545.2, R541.2, R542.1, R543.1, U53.3 (FB)
unnamed: C543.1, U53.14 (NR/SS)
unnamed: C67.2, RN61.6, RN61.7, RN61.8, U61.2 (-)
unnamed: R61.1, U61.6 (-), U61.7
unnamed: C777.1, C778.1, L77.2, U70.4 (Vcc)
unnamed: C722.1, R720.1, U74.8 (+)
unnamed: C723.2, R721.1, U74.1 (-)
unnamed: C764.2, R764.1, U75.2 (-)
unnamed: C760.1, R760.2, U75.5 (+)
unnamed: C761.2, R762.1, U75.6 (-)
unnamed: C704.2, R705.1, U77.2 (-)
unnamed: R707.1, R708.2, U78.2 (-)
unnamed: U81.9 (QH'), U82.14 (SER)
unnamed: R84.1, U84.12 (INC)
unnamed: R83.1, U84.13 (OUTB)
unnamed: C82.1, C83.1, L82.2, U84.1 (V_{CC})
unnamed: C85.1, C86.1, U84.16 (V_{ISO})
unnamed: C851.1, C854.1, L83.2, U85.7 (VDD)
unnamed: C302.2, R303.1, U301.2 (-)
unnamed: C306.2, R311.1, U301.6 (-)
unnamed: C329.2, R331.1, U321.2 (-)
unnamed: C312.2, R323.1, U321.6 (-)
unnamed: C342.2, R343.1, U341.2 (-)
unnamed: C345.2, R351.1, U341.6 (-)
unnamed: C366.2, R371.1, U361.2 (-)
unnamed: C362.2, R363.1, U361.6 (-)
unnamed: R709.1, R710.2, U704.2 (-)
unnamed: R711.1, R712.2, U704.6 (-)
unnamed: C729.2, R731.2, R732.1, U706.2 (-)
unnamed: C730.1, R735.1, R736.1, U706.6 (-)
PWR_EN: Q82.1 (G), R854.2, U8.20 (IO15)
Ref0V: C763.1, R62.2, R63.1, U75.3 (+)
Ref2V5: C728.1, R61.2, R62.1, U73.5 (+)
Ref5V: C64.1, C65.1, R113.1, R118.1, R315.2, R335.2, R356.2, R376.2, R760.1, TP62.1, U6.6 (OUTS), U6.7 (OUTF), U61.3 (+), U61.5 (+)
Ref7V5: C68.1, R68.2, R316.2, R336.2, R355.2, R375.2, RN61.1, RN61.2
USB_D+: J7.A6 (D+), J7.B6 (D+), U8.19 (IO14)
USB_D-: J7.A7 (D-), J7.B7 (D-), U8.18 (IO13)

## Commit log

2026-01-03 Work in progress. About to simplify resistor chain
2026-01-04 More work in progres
2026-01-10 Analog side is more or less complete.
2026-01-14 Little simplifications etc.
2026-01-14 Missed files
2026-01-16 Schematic complete, maybe
2026-01-16 Part selection
2026-01-18 ERC passes.
2026-01-19 Everything assigned except for wierd shit.
2026-01-19 Layout underway
2026-01-23 Whew. DACs routed
2026-01-29 Tweaks following spice simulation.
2026-02-04 About to delete scan...
2026-02-05 Scan deleted.
2026-02-08 Most blocks there....
    About to restore scan.
2026-02-08 S&H restored. Now to touch up connections etc.
2026-02-12 Put ref filtering into the schematic.
2026-02-13 Adjust voltage rails.
2026-02-16 Progress checkin. About to redo FDA feedback again.
2026-02-20 Start to place within physical board size.
2026-02-21 Adjust placements
2026-02-21 Remove silly jumpers.
2026-02-24 Power mostly routed
2026-02-26 Nearly all routed. Repinning FDA resistors.
2026-02-27 Put in some IO resistors.
2026-02-27 Deal to DRC errors.
2026-03-01 DRC update. Repin ADC. De-crack the S/H ground.
2026-03-01 Shuffle the monitor block about.
2026-03-01 Redo the SPI routing to DAC.
2026-03-01 Rationalise and more SPI tidy.
2026-03-01 Redo the reference ground star point.
2026-03-02 Remove placebo planes. Tidy some analog routing.
2026-03-02 More component metadata.
2026-03-05 Front panel
2026-03-05 Back panel
2026-03-06 Contact pads. Shuffle the big cap.
2026-03-06 Change some footprints.
    Mounting holes for covers.
2026-03-06 Clean all remaining DRC issues.
2026-03-06 Tweaks and simplification.
2026-03-07 Protection on ground drives.
2026-03-08 Simplify relay drive.
2026-03-08 Redo the DAC ground drive yet again.
2026-03-09 Add some bulk capacitance.
2026-03-09 Component tweak.
2026-03-10 Tweak various feedback loops.
2026-03-13 Readyish
2026-03-17 Add solder practice. Final touchups.
2026-03-18 Capacitor tweak.
2026-03-18 Fix solder mask on a component.
2026-03-18 DRC exclusions (sigh).
